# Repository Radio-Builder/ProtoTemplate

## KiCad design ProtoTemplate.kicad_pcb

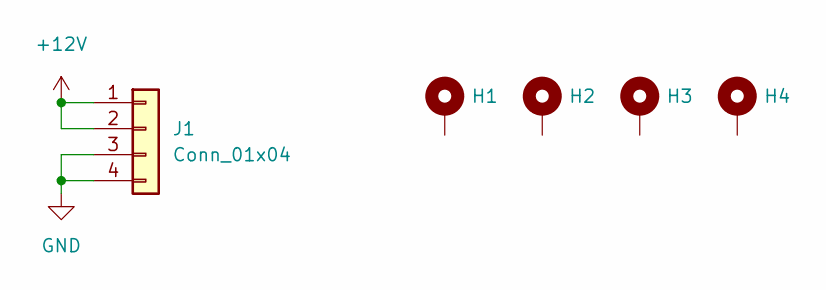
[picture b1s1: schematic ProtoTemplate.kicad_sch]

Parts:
H1, H2, H3, H4: MountingHole_Pad; TestPoint_Plated_Hole_D3.0mm
J1: Conn_01x04; PinSocket_1x04_P2.54mm_Vertical

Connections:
+12V: J1.1, J1.2
GND: J1.3, J1.4

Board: 2 copper layers, 5 parts (0 on the bottom side), 2 nets, no tracks yet.
